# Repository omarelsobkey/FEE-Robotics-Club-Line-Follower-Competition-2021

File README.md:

# Robotics-FEE-Competition-2021

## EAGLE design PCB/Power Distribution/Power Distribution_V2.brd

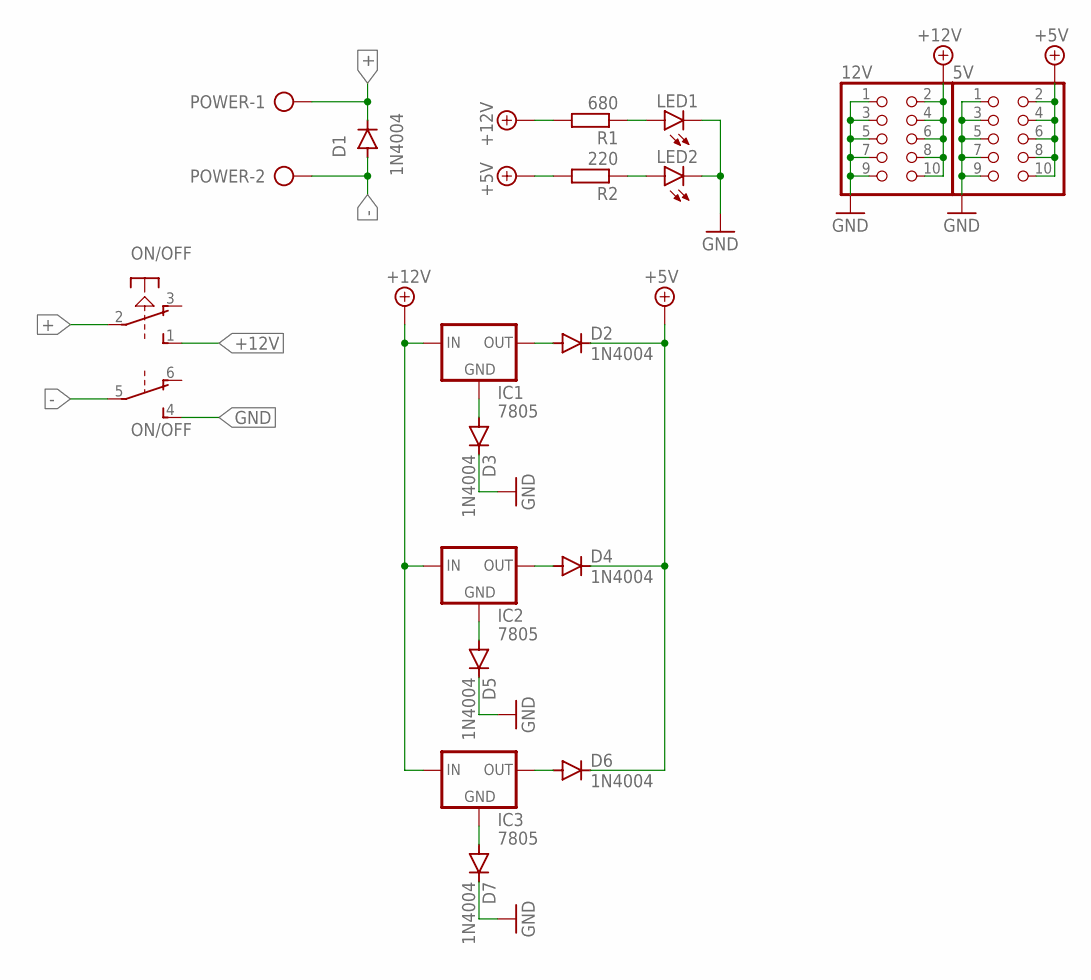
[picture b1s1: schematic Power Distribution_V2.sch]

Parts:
5V, 12V: PINHD-2X5; 2X05
D1, D2, D3, D4, D5, D6, D7: 1N4004; DO41-10
IC1, IC2, IC3: 7805; 78XXS
LED1, LED2: LED3MM
ON/OFF: PVA2R
POWER: AK500/2-H
R1: 680; 0207/10
R2: 220; 0207/10

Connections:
+: D1.C, ON/OFF.2, POWER.1
+5V: 5V.2, 5V.4, 5V.6, 5V.8, 5V.10, D2.C, D4.C, D6.C, R2.2
+12V: 12V.2, 12V.4, 12V.6, 12V.8, 12V.10, IC1.IN, IC2.IN, IC3.IN, ON/OFF.1 (S), R1.2
-: D1.A, ON/OFF.5, POWER.2
GND: 5V.1, 5V.3, 5V.5, 5V.7, 5V.9, 12V.1, 12V.3, 12V.5, 12V.7, 12V.9, D3.C, D5.C, D7.C, LED1.K (C), LED2.K (C), ON/OFF.4 (S)
unnamed: LED1.A, R1.1
unnamed: D7.A, IC3.GND
unnamed: LED2.A, R2.1
unnamed: D5.A, IC2.GND
unnamed: D3.A, IC1.GND
unnamed: D2.A, IC1.OUT
unnamed: D6.A, IC3.OUT
unnamed: D4.A, IC2.OUT

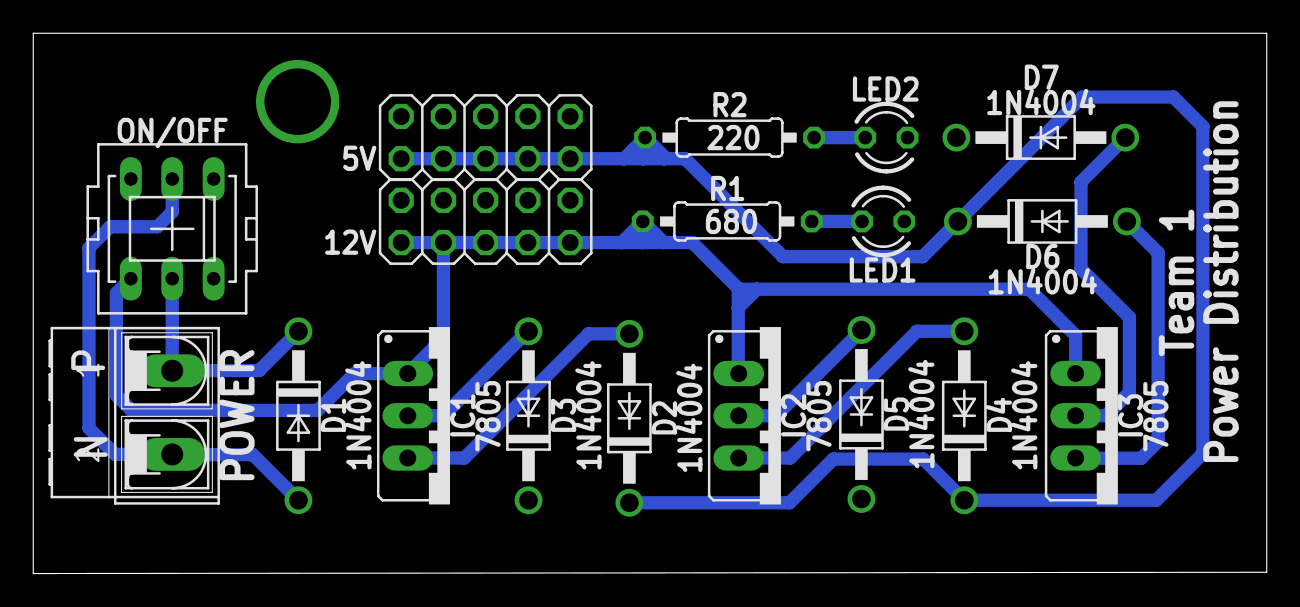
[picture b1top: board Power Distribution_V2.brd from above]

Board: 2 copper layers, 74.2 x 32.5 mm, 18 parts (0 on the bottom side), 13 nets.

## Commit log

2021-07-02 Upload all the project data
2021-07-02 add the remaining files.
2021-07-02 restore README file.
